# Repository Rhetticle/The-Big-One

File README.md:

# The Big One

https://github.com/user-attachments/assets/869daa6d-89cc-4672-a1f7-7d603dca1637

3D printed 3-stage 1kJ projectile accelerator.

## Update
As of Febuary 2024, this device is no longer operational and has been salvaged for parts.
## Safety Notice
* This device was built purely to challenge myself with a complex engineering project to learn about electronics and was never intended to be used as a weapon
* Certain parts of the build have been omitted from the repository to prevent those with malicious intent from replicating this device
## Performance
* Peak exit velocity (All capacitors charged to 385V) - 61 km/h
* Peak exit energy (100g projectile) - 13.9 J
* Efficiency - 1.4%

## Hardware Details
All circuitry and PCBs were custom made, designed in Kicad and manufactured by JLCPCB with hardware provided by Digikey or homemade (e.g. transformer, power inductors etc)
### Capacitors
The Big One uses three 4.5mF 400V chassis mount capacitors. The total energy in these capacitors at max operating voltage (385V) is approximately 1kJ. 
### Capacitor Charger
Capacitors were charged using a ZVS circuit driving a homemade step-up transformer (see below) to increase the 30VAC across the resonant capacitors of the ZVS up to 550VAC to be used to charge the high voltage capacitors. The average power output of this charger was around 300W when charging the entire bank of capacitors from 0V to 385V. 

### Control Board
The control board was mounted in the middle section. It uses an STM32F401RBT6 to control the timing of the three acceleration stages as well as measures the capacitor bank voltage. Four schottky diodes are also on the board to rectify the transformer output.

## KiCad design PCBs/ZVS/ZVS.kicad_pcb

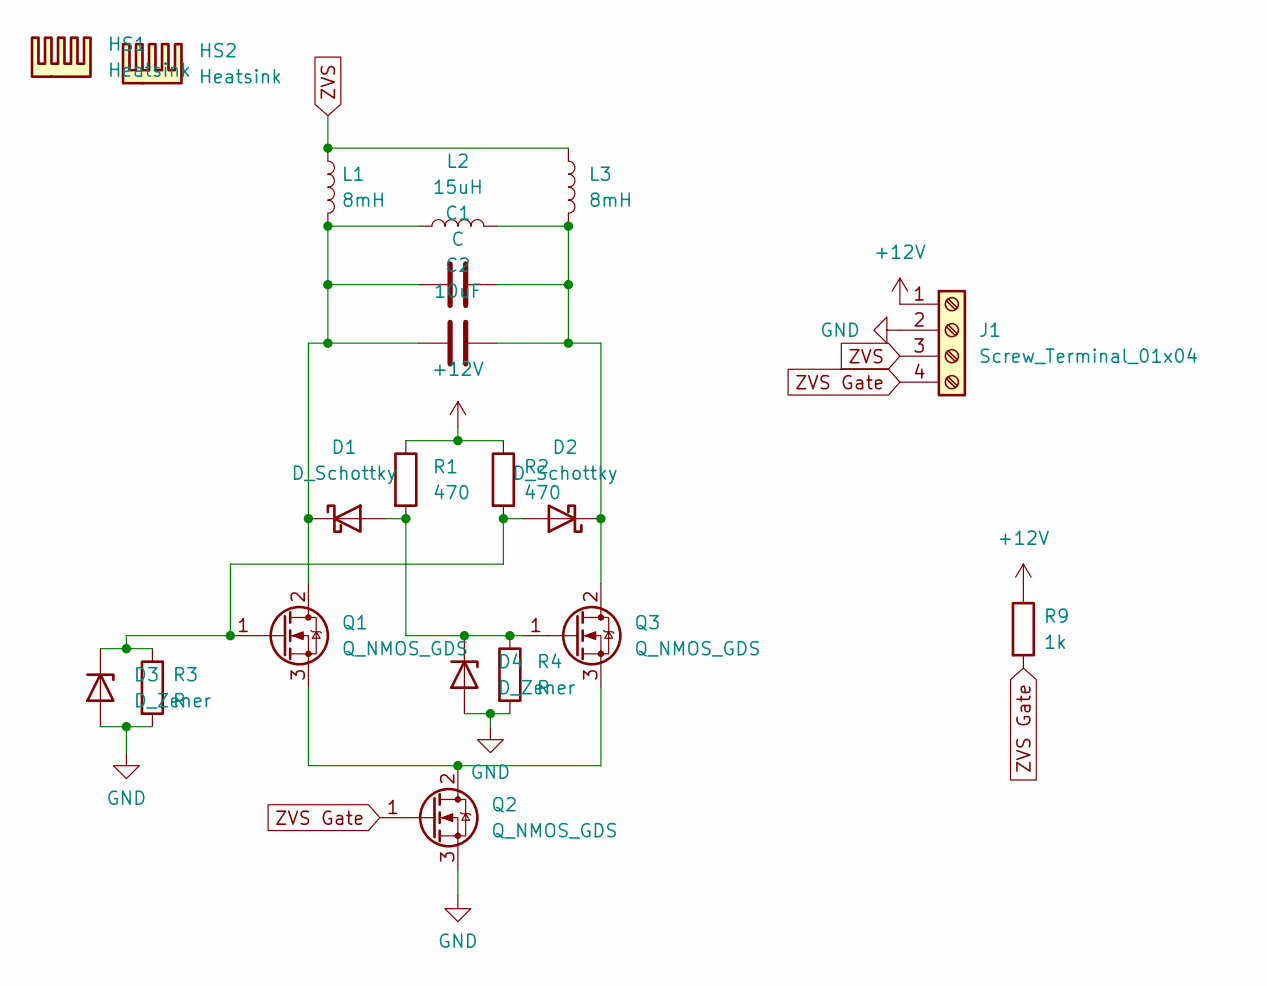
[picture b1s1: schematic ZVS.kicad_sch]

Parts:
C1: C; C_Rect_L26.5mm_W11.5mm_P22.50mm_MKS4
C2: 10uF; C_Rect_L26.5mm_W11.5mm_P22.50mm_MKS4
D1, D2: D_Schottky; D_DO-201_P12.70mm_Horizontal
D3, D4: D_Zener; D_DO-35_SOD27_P7.62mm_Horizontal
HS1, HS2: Heatsink; 63710ABPE
J1: Screw_Terminal_01x04; TerminalBlock_bornier-4_P5.08mm
L1, L3: 8mH; L_Toroid_Vertical_L26.7mm_W14.0mm_P10.16mm_Pulse_D
L2: 15uH; Primary
Q1, Q2, Q3: Q_NMOS_GDS; TO-220-3_Vertical
R1, R2: 470; R_Axial_DIN0617_L17.0mm_D6.0mm_P20.32mm_Horizontal
R3, R4: R; R_Axial_DIN0204_L3.6mm_D1.6mm_P7.62mm_Horizontal
R9: 1k; R_Axial_DIN0204_L3.6mm_D1.6mm_P7.62mm_Horizontal

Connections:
+12V: J1.1, R1.1, R2.1, R9.1
GND: D3.2 (A), D4.2 (A), J1.2, Q2.3 (S), R3.2, R4.2
unnamed: C1.1, C2.1, D1.1 (K), L1.2, L2.1, Q1.2 (D)
unnamed: C1.2, C2.2, D2.1 (K), L2.2, L3.2, Q3.2 (D)
unnamed: D1.2 (A), D4.1 (K), Q3.1 (G), R1.2, R4.1
unnamed: D2.2 (A), D3.1 (K), Q1.1 (G), R2.2, R3.1
unnamed: Q1.3 (S), Q2.2 (D), Q3.3 (S)
ZVS: J1.3, L1.1, L3.1
ZVS Gate: J1.4, Q2.1 (G), R9.2

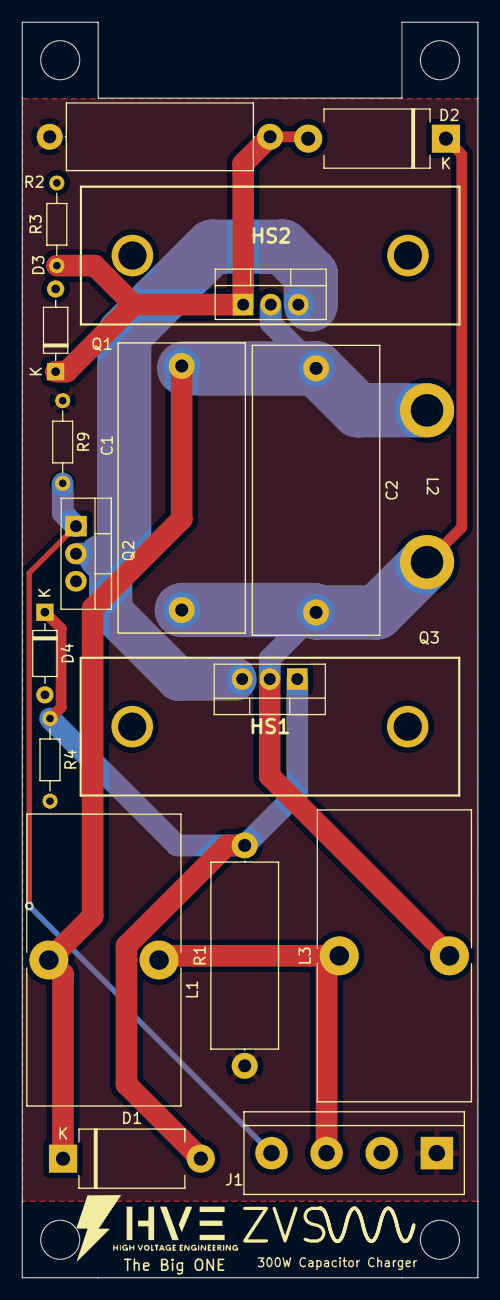
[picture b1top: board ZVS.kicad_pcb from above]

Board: 2 copper layers, 42.0 x 115.8 mm, 20 parts (0 on the bottom side), 9 nets.

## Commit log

2024-03-29 Formatting
2024-03-29 Added firmware
